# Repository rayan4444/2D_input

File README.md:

# 2D Input on any surface

Eagle files Repository for 2D input project

## Modular version
Based on ESP32 to test different hardware configurations. One PCB design that can be snapped to separate core and peripheral modules. Test code available.

## Downsized version
Based on NRF52 as a first step to real manufacturing size. Firmware not available

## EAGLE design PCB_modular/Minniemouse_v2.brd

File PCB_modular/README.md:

# 2D Input on any surface - Modular PCB

## Features
Modular version - Core
* ESP32-WROOM32 Module
* CP2104 USB-UART bridge
* 1S Li-Po charger
* 3.3V LDO
* 2x FPC breakout connectors

Modular version - Peripherals
* MPU9250 IMU
* Custom narrow angle IR sensor ( & )
* 2x buttons
* Capacitive touch sensor board (3 positions)
* Joystick

## Hardware connections

|Signal| Arduino Pin|Note|
|:---:|:---:|:---:|
|RXD0|RXD0|Programming|
|TXD0|TXD0|Programming|
|IMU_SDA|23|
|IMU_SCL|22|
|BUTTON 1 or CAP_TOUCH_1|14, A6||
|BUTTON 2|15||
|CAP_TOUCH_2 or JOY_X|33, A9||
|CAP_TOUCH_3 or JOY_Y|32, A7||
|LED|13||
|IR_LED|12||
|IR_SENSOR_OUT|34, A2|Analog|

## Programming
Follow normal Arduino for ESP32 instructions. Select "Adafruit feather" as Board in Arduino IDE to program.

## Errata
* MPU9250 is discontinued - don't use it for any new designs
* Problem: cannot connect to the MCU to flash it.   
    * Solution: Missing trace on GPIO0 line that connects to the auto-reset circuit. Used a rework wire as a temporary fix.

## References & tutorials
* [MPU4920 datasheet]()
* [Capacitive touch sensor design guide]()

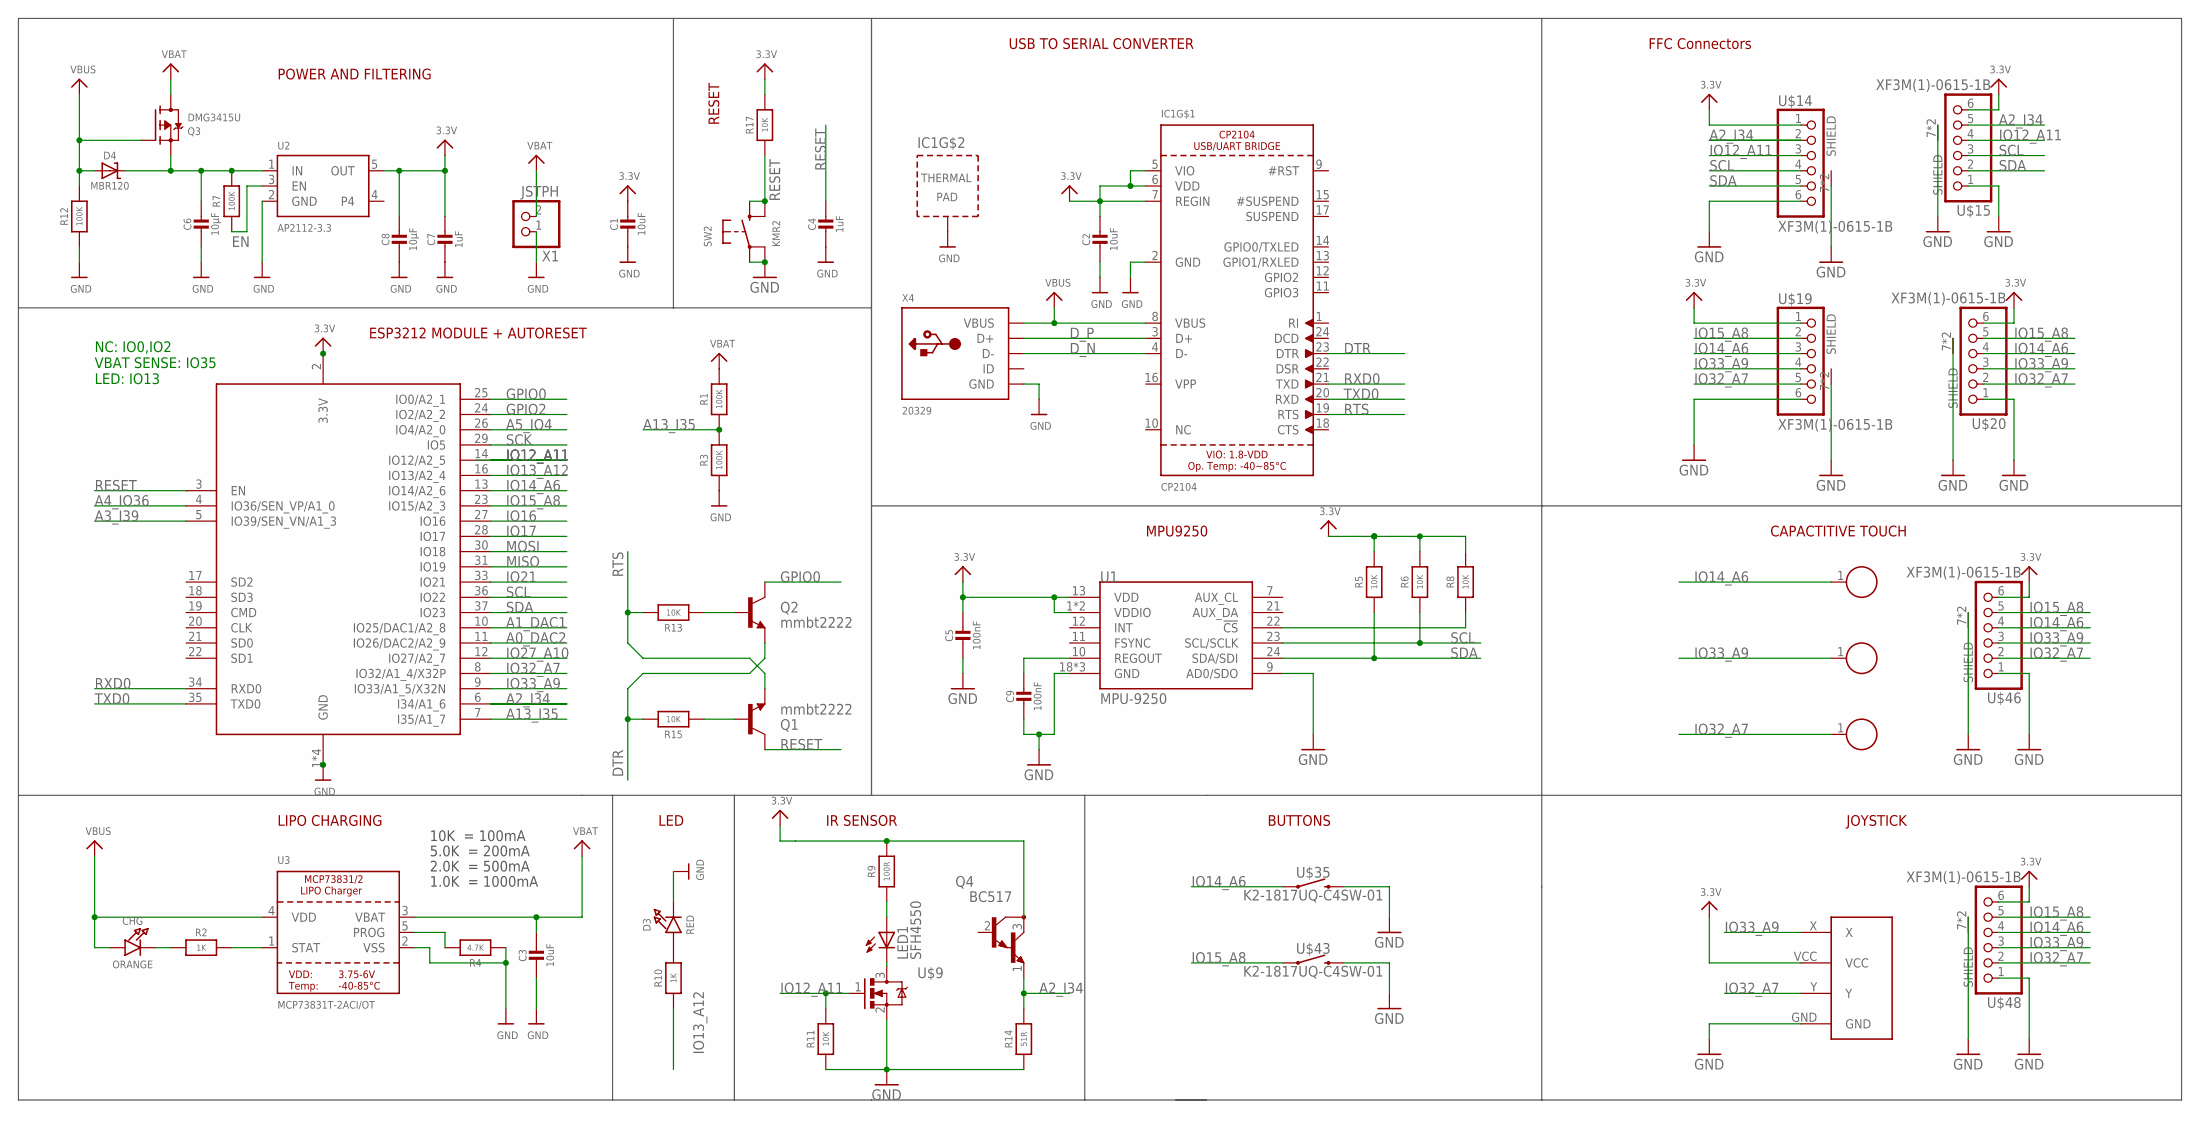
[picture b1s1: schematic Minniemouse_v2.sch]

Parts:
C1, C2, C3: 10uF; _0402
C4, C7: 1uF; _0402
C5, C9: 100nF; _0402
C6, C8: 10µF; _0402
CHG: ORANGE; CHIPLED_0805_NOOUTLINE
D3: RED; CHIPLED_0805_NOOUTLINE
D4: MBR120; SOD-123
IC1: CP2104; QFN24_4MM_SMSC
LED1: SFH4550; LED_LED5MM
P1, P2, P3: CAPTOUCH_PAD; CAPTOUCH_6.5X7
Q1, Q2: mmbt2222; SOT23-3
Q3: DMG3415U; SOT23-R
Q4: BC517; TO92
R1, R3, R7, R12: 100K; _0402
R2, R10: 1K; _0402
R4: 4.7K; _0402
R5, R6, R8, R11, R13, R15, R17: 10K; _0402
R9: 100R; _0402
R14: 51R; _0402
SW2: KMR2; BTN_KMR2_4.6X2.8
U1: MPU-9250; QFN24_PAD
U2: AP2112-3.3; SOT23-5
U3: MCP73831T-2ACI/OT; SOT23-5
U$9: DMN6140L; SOT91P240X110-3N
U$14, U$15, U$19, U$20, U$46, U$48: XF3M(1)-0615-1B
U$35, U$43: K2-1817UQ-C4SW-01
U$49: JOYSTICK
X1: JSTPH; JSTPH2
X2: ESP32_WROOM32_SKINNY; WROOM32_SKINNY
X4: 20329; 4UCONN_20329_V2

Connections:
3.3V: C1.1, C2.1, C5.1, C7.1, C8.1, IC1.5 (VIO), IC1.6 (VDD), IC1.7 (REGIN), Q4.3 (C), R5.2, R6.2, R8.2, R9.2, R17.2, U1.1 (VDDIO), U1.8 (VDDIO), U1.13 (VDD), U2.5 (OUT), U$14.1, U$15.6, U$19.1, U$20.6, U$46.6, U$48.6, U$49.VCC, X2.2 (3.3V)
!CS: R8.1, U1.22 (!CS)
A0_DAC2: X2.11 (IO26/DAC2/A2_9)
A1_DAC1: X2.10 (IO25/DAC1/A2_8)
A2_I34: Q4.1 (E), R14.2, U$14.2, U$15.5, X2.6 (I34/A1_6)
A3_I39: X2.5 (IO39/SEN_VN/A1_3)
A4_IO36: X2.4 (IO36/SEN_VP/A1_0)
A5_IO4: X2.26 (IO4/A2_0)
A13_I35: R1.1, R3.2, X2.7 (I35/A1_7)
DTR: IC1.23 (DTR), Q2.2 (E), R15.2
D_N: IC1.4 (D-), X4.D-
D_P: IC1.3 (D+), X4.D+
EN: R7.1, U2.3 (EN)
GND: C1.2, C2.2, C3.2, C4.2, C5.2, C6.2, C7.2, C8.2, C9.2, D3.C, IC1.2 (GND), IC1.THERM (TP), R3.1, R4.1, R11.1, R12.1, R14.1, SW2.A, SW2.A' (P1), U1.9 (AD0/SDO), U1.18 (GND), U1.20 (GND), U1.CENTER (GND), U2.2 (GND), U3.2 (VSS), U$9.2, U$14.6, U$14.7 (SHIELD), U$14.8 (SHIELD), U$15.1, U$15.7 (SHIELD), U$15.8 (SHIELD), U$19.6, U$19.7 (SHIELD), U$19.8 (SHIELD), U$20.1, U$20.7 (SHIELD), U$20.8 (SHIELD), U$35.P$2 (2), U$43.P$2 (2), U$46.1, U$46.7 (SHIELD), U$46.8 (SHIELD), U$48.1, U$48.7 (SHIELD), U$48.8 (SHIELD), U$49.GND, X1.1, X2.1 (GND), X2.15 (GND), X2.38 (GND), X2.P$1 (GND), X4.BASE@1 (GND), X4.BASE@2 (GND), X4.GND, X4.SPRT@1 (GND), X4.SPRT@2 (GND), X4.SPRT@3 (GND), X4.SPRT@4 (GND)
GPIO0: Q2.3 (C), X2.25 (IO0/A2_1)
GPIO2: X2.24 (IO2/A2_2)
IO12_A11: R11.2, U$9.1, U$14.3, U$15.4, X2.14 (IO12/A2_5)
IO13_A12: R10.1, X2.16 (IO13/A2_4)
IO14_A6: P1.1, U$19.3, U$20.4, U$35.P$1 (1), U$46.4, U$48.4, X2.13 (IO14/A2_6)
IO15_A8: U$19.2, U$20.5, U$43.P$1 (1), U$46.5, U$48.5, X2.23 (IO15/A2_3)
IO16: X2.27 (IO16)
IO17: X2.28 (IO17)
IO21: X2.33 (IO21)
IO27_A10: X2.12 (IO27/A2_7)
IO32_A7: P3.1, U$19.5, U$20.2, U$46.2, U$48.2, U$49.Y, X2.8 (IO32/A1_4/X32P)
IO33_A9: P2.1, U$19.4, U$20.3, U$46.3, U$48.3, U$49.X, X2.9 (IO33/A1_5/X32N)
MISO: X2.31 (IO19)
MOSI: X2.30 (IO18)
unnamed: CHG.C, R2.1
unnamed: R2.2, U3.1 (STAT)
unnamed: R4.2, U3.5 (PROG)
unnamed: D3.A, R10.2
unnamed: C6.1, D4.C, Q3.2 (S), R7.2, U2.1 (IN)
unnamed: Q2.1 (B), R13.1
unnamed: LED1.A, R9.1
unnamed: LED1.K (C), U$9.3
unnamed: Q1.1 (B), R15.1
REGOUT: C9.1, U1.10 (REGOUT)
RESET: C4.1, Q1.3 (C), R17.1, SW2.B (S), SW2.B' (S1), X2.3 (EN)
RTS: IC1.19 (RTS), Q1.2 (E), R13.2
RXD0: IC1.21 (TXD), X2.34 (RXD0)
SCK: X2.29 (IO5)
SCL: R6.1, U1.23 (SCL/SCLK), U$14.4, U$15.3, X2.36 (IO22)
SDA: R5.1, U1.24 (SDA/SDI), U$14.5, U$15.2, X2.37 (IO23)
TXD0: IC1.20 (RXD), X2.35 (TXD0)
VBAT: C3.1, Q3.3 (D), R1.2, U3.3 (VBAT), X1.2
VBUS: CHG.A, D4.A, IC1.8 (VBUS), Q3.1 (G), R12.2, U3.4 (VDD), X4.VBUS

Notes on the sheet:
POWER AND FILTERING
RESET
10K = 100mA
5.0K = 200mA
2.0K = 500mA
1.0K = 1000mA
USB TO SERIAL CONVERTER
LIPO CHARGING
LED
ESP3212 MODULE + AUTORESET
NC: IO0,IO2 VBAT SENSE: IO35 LED: IO13
MPU9250
IR SENSOR
BUTTONS
FFC Connectors
CAPACTITIVE TOUCH
JOYSTICK

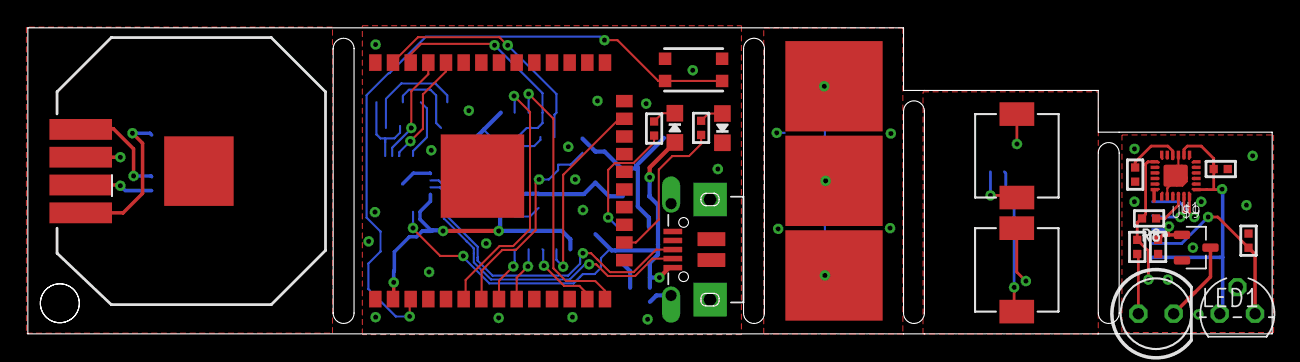
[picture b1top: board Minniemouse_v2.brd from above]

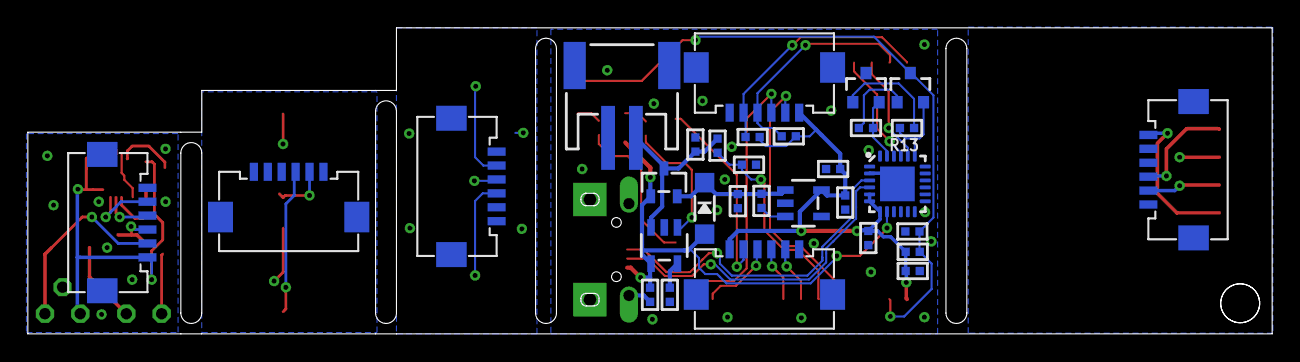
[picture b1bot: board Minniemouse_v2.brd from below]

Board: 2 copper layers, 89.4 x 22.0 mm, 54 parts (31 on the bottom side), 34 nets.

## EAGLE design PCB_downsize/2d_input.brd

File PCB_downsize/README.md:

# 2D Input on any surface - Downsized PCB

## Features
* NRF52 (BMD350 module)
* SWD Programming & debugging port
* 1S Li-Po charger
* 3.3V & 1.8V LDO
* MPU9250 IMU
* VCNL36687S Proximity sensor

## Hardware connections

|Signal|Pin|Note|
|:---:|:---:|:---:|
|RESET|21||
|INT_IMU|17||
|INT_IR|30||
|SDA|6||
|SCL|8||

## Debugging notes
* VCNL36687S soldered at 90 deg: one side pins soldered, other side using rework wire
* Add connector to external button in next version

## Programming
* Didn't get permission to share firmware
* [NRF52 dev with visual studio code](https://github.com/rayan4444/vs_code_setup_tutorials/tree/master/NRF52)

## Datasheets
* [BMD350](https://www.u-blox.com/sites/default/files/BMD-350_DataSheet_%28UBX-19033354%29.pdf)
* [MPU9250](https://invensense.tdk.com/wp-content/uploads/2015/02/PS-MPU-9250A-01-v1.1.pdf)
* [VCNL36687S](https://www.vishay.com/docs/84907/vcnl36687s.pdf)

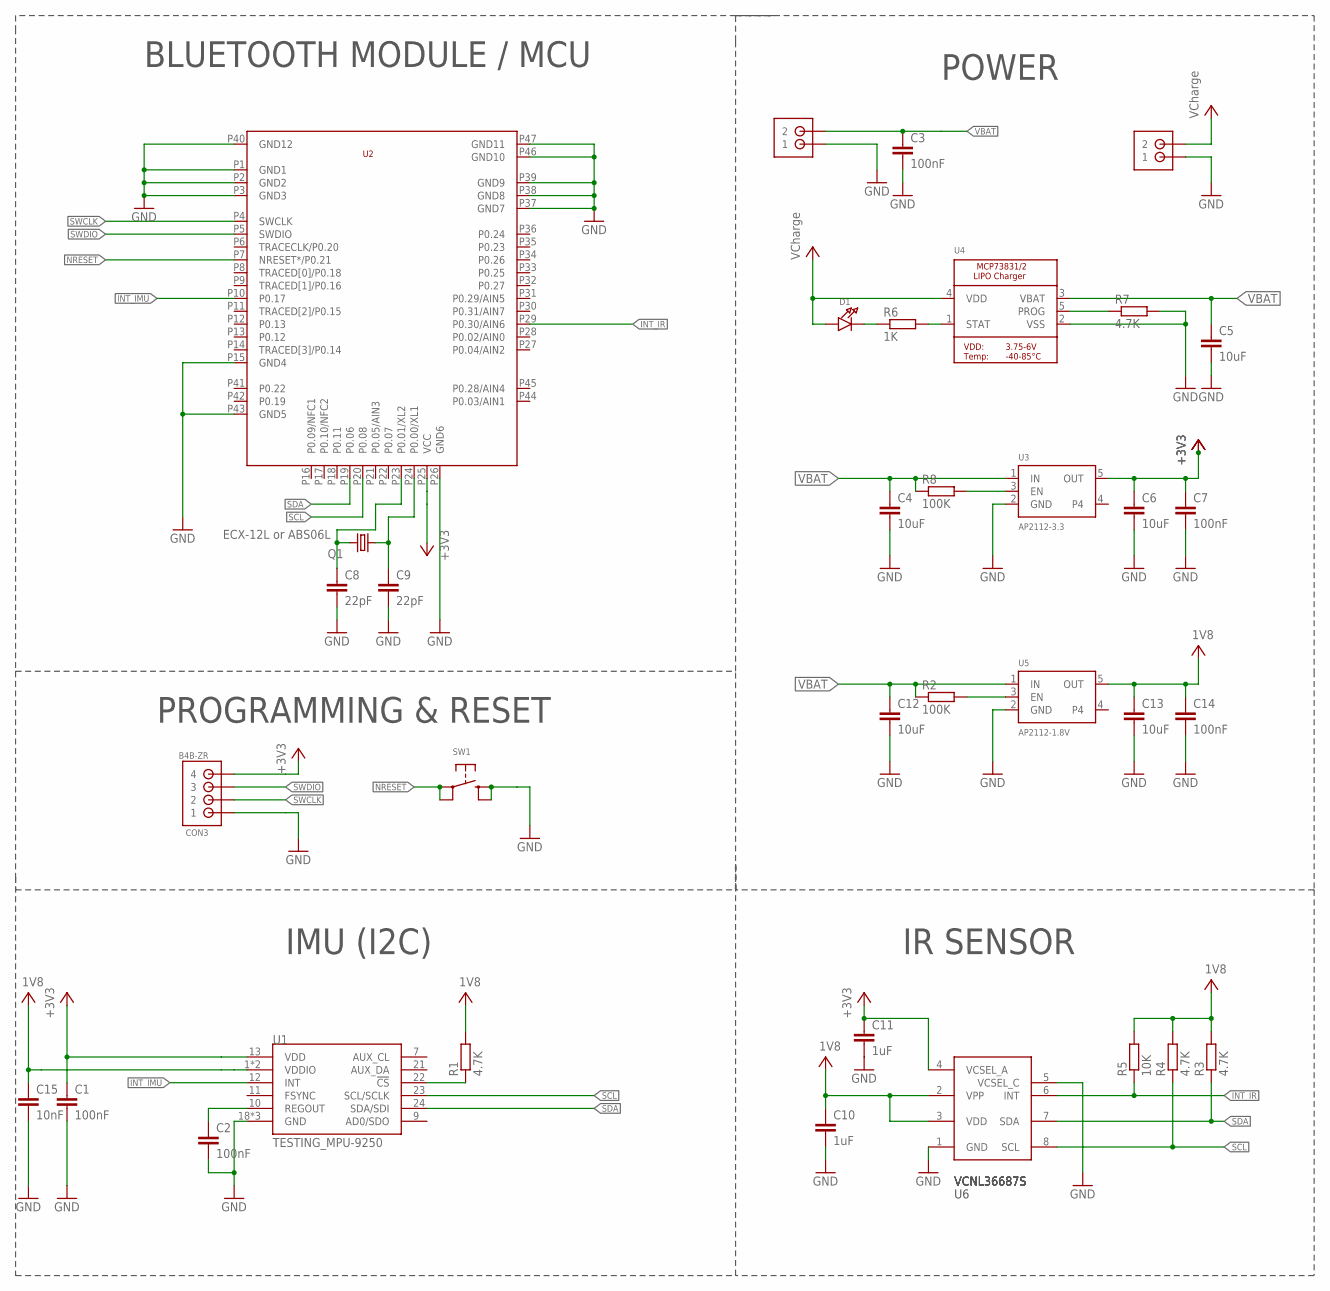
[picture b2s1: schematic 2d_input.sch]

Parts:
C1, C2, C3, C7, C14: 100nF; C0402K
C4, C5, C6, C12, C13: 10uF; C0402K
C8, C9: 22pF; C0402K
C10, C11: 1uF; C0402K
C15: 10nF; C0402K
CON1, CON2: B2B-ZR
CON3: B4B-ZR
D1: MICROBUILDER_LED0603_NOOUTLINE; MICROBUILDER_CHIPLED_0603_NOOUTLINE
Q1: ECX-12L or ABS06L; 2.0X1.2
R1, R3, R4, R7: 4.7K; R0402
R2, R8: 100K; R0402
R5: 10K; R0402
R6: 1K; R0402
SW1: MICROBUILDER_SWITCH_TACT_SMT4.6X2.8; MICROBUILDER_BTN_KMR2_4.6X2.8
U1: TESTING_MPU-9250; TESTING_QFN24_PAD
U2: BMD-350
U3: AP2112-3.3; MICROBUILDER_SOT23-5
U4: MICROBUILDER_MCP73831/2; MICROBUILDER_SOT23-5
U5: AP2112-1.8V; MICROBUILDER_SOT23-5
U6: VCNL36687S

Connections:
+3V3: C1.1, C6.1, C7.1, C11.1, CON3.4, U1.13 (VDD), U2.P25 (VCC), U3.5 (OUT), U6.4 (VCSEL_A)
GND: C1.2, C2.2, C3.2, C4.2, C5.2, C6.2, C7.2, C8.2, C9.2, C10.2, C11.2, C12.2, C13.2, C14.2, C15.2, CON1.1, CON2.1, CON3.1, R7.2, SW1.B (S), SW1.B' (S1), U1.18 (GND), U1.20 (GND), U1.CENTER (GND), U2.P1 (GND1), U2.P2 (GND2), U2.P3 (GND3), U2.P15 (GND4), U2.P26 (GND6), U2.P37 (GND7), U2.P38 (GND8), U2.P39 (GND9), U2.P40 (GND12), U2.P43 (GND5), U2.P46 (GND10), U2.P47 (GND11), U3.2 (GND), U4.2 (VSS), U5.2 (GND), U6.1 (GND), U6.5 (VCSEL_C)
INT_IMU: U1.12 (INT), U2.P10 (P0.17)
INT_IR: R5.1, U2.P29 (P0.30/AIN6), U6.6 (INT)
unnamed: C2.1, U1.10 (REGOUT)
unnamed: R7.1, U4.5 (PROG)
unnamed: C9.1, Q1.1, U2.P24 (P0.00/XL1)
unnamed: R1.1, U1.22 (!CS)
unnamed: R6.2, U4.1 (STAT)
unnamed: D1.C, R6.1
unnamed: R8.2, U3.3 (EN)
unnamed: R2.2, U5.3 (EN)
unnamed: C8.1, Q1.2, U2.P23 (P0.01/XL2)
NRESET: SW1.A, SW1.A' (P1), U2.P7 (NRESET*/P0.21)
SCL: R4.1, U1.23 (SCL/SCLK), U2.P20 (P0.08), U6.8 (SCL)
SDA: R3.1, U1.24 (SDA/SDI), U2.P19 (P0.06), U6.7 (SDA)
SWCLK: CON3.2, U2.P4 (SWCLK)
SWDIO: CON3.3, U2.P5 (SWDIO)
V+: C10.1, C13.1, C14.1, C15.1, R1.2, R3.2, R4.2, R5.2, U1.1 (VDDIO), U1.8 (VDDIO), U5.5 (OUT), U6.2 (VPP), U6.3 (VDD)
VBAT: C3.1, C4.1, C5.1, C12.1, CON1.2, R2.1, R8.1, U3.1 (IN), U4.3 (VBAT), U5.1 (IN)
VCC: CON2.2, D1.A, U4.4 (VDD)

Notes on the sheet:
BLUETOOTH MODULE / MCU
IMU (I2C)
IR SENSOR
POWER
PROGRAMMING & RESET
VCNL36687S

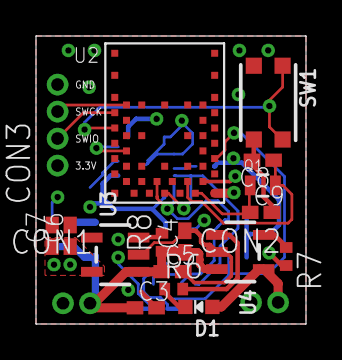
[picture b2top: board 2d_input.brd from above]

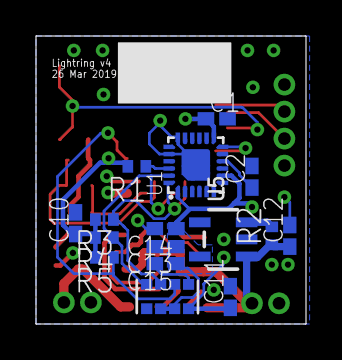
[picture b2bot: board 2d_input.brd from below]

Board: 4 copper layers, 15.0 x 16.0 mm, 35 parts (16 on the bottom side), 21 nets.

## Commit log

2020-08-12 Post project commit

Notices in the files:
parts and their libraries:
crystal-geyer_V1_0: Copyright: Geyer-Electronic
microbuilder: This work is placed in the public domain, and may be freely used for commercial and non-commercial work with the following conditions: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
SparkFun: Licensing: CC v3.0 Share-Alike You are welcome to use this library for commercial purposes.
